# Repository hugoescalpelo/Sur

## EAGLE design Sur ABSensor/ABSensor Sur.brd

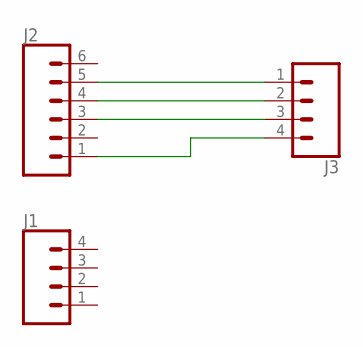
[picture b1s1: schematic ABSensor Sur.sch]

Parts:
J1, J3: CONN_04LONGPADS; 1X04_LONGPADS
J2: CONN_06LONGPADS; 1X06_LONGPADS

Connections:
unnamed: J2.1, J3.4
unnamed: J2.3, J3.3
unnamed: J2.4, J3.2
unnamed: J2.5, J3.1

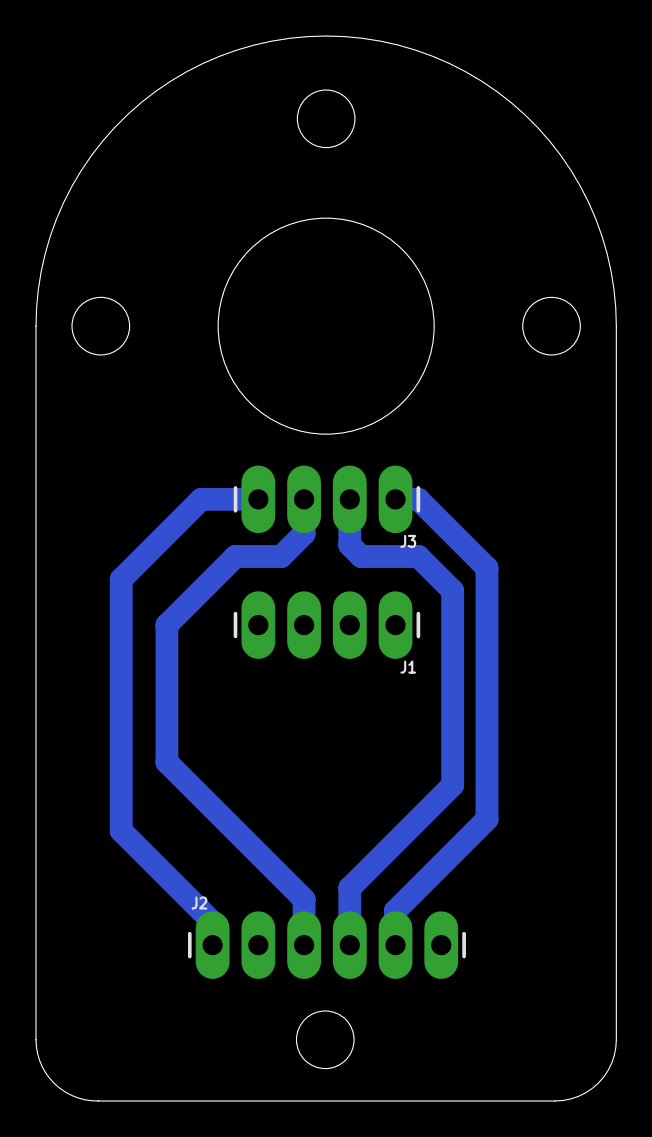
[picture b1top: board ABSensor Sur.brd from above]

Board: 2 copper layers, 32.2 x 59.2 mm, 3 parts (0 on the bottom side), 4 nets.

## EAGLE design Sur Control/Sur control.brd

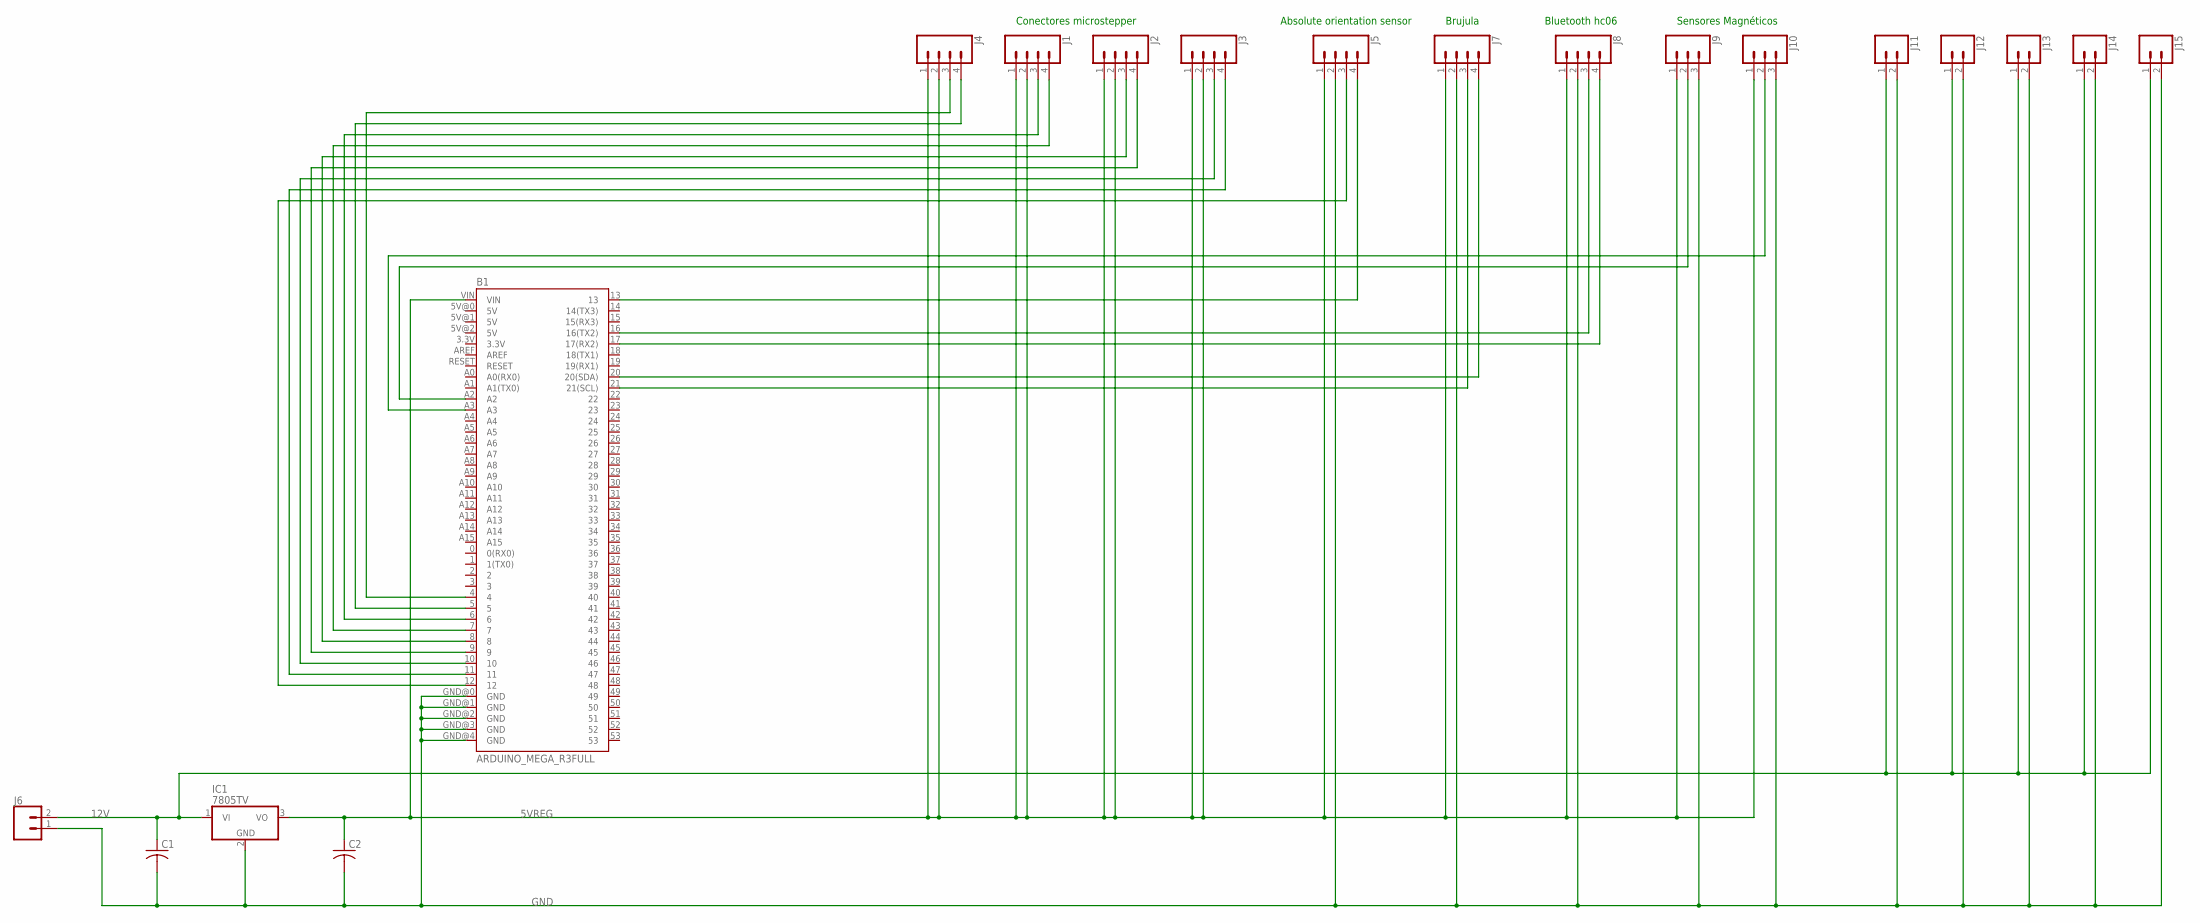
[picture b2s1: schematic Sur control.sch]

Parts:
B1: ARDUINO_MEGA_R3FULL; ARDUINO_MEGA
C1, C2: C-US050-025X075; C050-025X075
IC1: 7805TV; TO220V
J1, J2, J3, J4, J5, J7, J8: CONN_04SCREW_LOCK; SCREWTERMINAL-3.5MM-4_LOCK
J6, J11, J12, J13, J14, J15: CONN_023.5MM_LOCK; SCREWTERMINAL-3.5MM-2_LOCK
J9, J10: CONN_03SCREW_LOCK; SCREWTERMINAL-3.5MM-3_LOCK.007S

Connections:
5VREG: B1.VIN, C2.1, IC1.3 (VO), J1.1, J1.2, J2.1, J2.2, J3.1, J3.2, J4.1, J4.2, J5.1, J7.1, J8.1, J9.1, J10.1
12V: C1.1, IC1.1 (VI), J6.2, J11.1, J12.1, J13.1, J14.1, J15.1
GND: B1.GND@0 (GND), B1.GND@1 (GND), B1.GND@2 (GND), B1.GND@3 (GND), B1.GND@4 (GND), C1.2, C2.2, IC1.2 (GND), J5.2, J6.1, J7.2, J8.2, J9.3, J10.3, J11.2, J12.2, J13.2, J14.2, J15.2
unnamed: B1.21 (21(SCL)), J7.3
unnamed: B1.20 (20(SDA)), J7.4
unnamed: B1.4, J4.3
unnamed: B1.5, J4.4
unnamed: B1.6, J1.3
unnamed: B1.7, J1.4
unnamed: B1.8, J2.3
unnamed: B1.9, J2.4
unnamed: B1.10, J3.3
unnamed: B1.11, J3.4
unnamed: B1.12, J5.3
unnamed: B1.13, J5.4
unnamed: B1.16 (16(TX2)), J8.3
unnamed: B1.17 (17(RX2)), J8.4
unnamed: B1.A2, J9.2
unnamed: B1.A3, J10.2

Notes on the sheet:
Conectores microstepper
Absolute orientation sensor
Bluetooth hc06
Brujula
Sensores Magnéticos

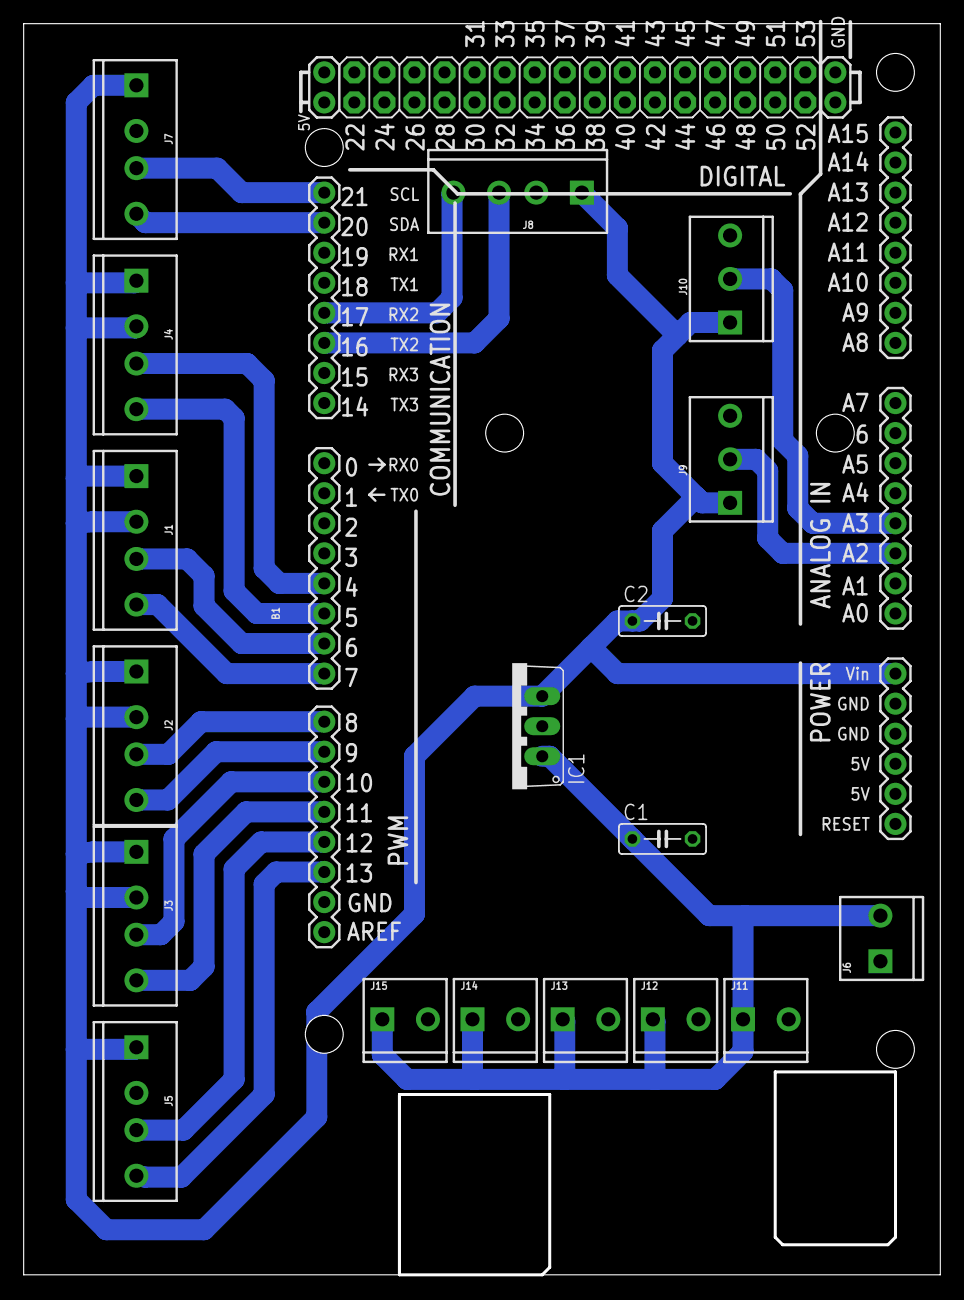
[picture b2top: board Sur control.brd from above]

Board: 2 copper layers, 77.5 x 105.7 mm, 19 parts (0 on the bottom side), 19 nets.

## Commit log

2018-06-25 Some code added
2018-06-28 Firt stepper test
2018-07-03 test a single motor
2018-07-03 L&R motor test added
2018-07-03 Test three motors both directions
2018-07-03 BNO055 sensor code added
    Not tested, but oh boy! it compiles!
2018-07-03 Shortest way sequence coded
    Checks the shortest way to turn the body and set direction and active run flag for all motors
2018-07-03 Continuous movement added
    Iterative on loop asynchronous all motors running sequence
2018-07-03 Pin sensor Added
    Just definition of pins for sensors
2018-07-05 Sensor compass calibration
    Sensor compass calibration sequence adderd. Logic is there but a change detector is needed
2018-07-06 Motor fixes
    Fix some major problems with motor logic. Change direction and pushh pull for reducer steppers
2018-07-09 BT control menu
    Test is pendant
2018-07-17 Sensor lecture tested
    We are in production process, so the machine is working and wired. Some BT and Hall test are done and working. Lots of changes added.
2018-07-18 Compass detection built
2018-07-18 Absolute orientation sensor tested
2018-07-19 MPV done
    Minimum Product Viable finished and tested. Some cool sequences left to be added. I want a speed gradient, maybe Ivan wants tone sounds for the reducers. ABSensor and compass orientation left to be t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
2018-07-19 loose tense tested
2018-07-24 Minor orientation bug fixes
2018-08-02 Changeloge updated
2018-08-13 Sintax fixed

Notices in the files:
parts and their libraries:
SparkFun-Connectors: Licensing: Creative Commons ShareAlike 4.0 International - https://creativecommons.org/licenses/by-sa/4.0
